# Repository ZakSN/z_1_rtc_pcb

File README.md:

this repo has the kicad board files for the z_1 RTC, a (hopefully very accurate)
real time clock. read more about it here: https://hackaday.io/project/180005-a-digital-real-time-clock

technically this is the 3rd version of the PCBs for this project, howerver the
first 2 versions didn't work well enough to bother publishing.

there are also 3 minor versions of the version 3 PCB:
- 3.1 LCMXO2-1200HC-4SG32C on the board (didn't work for mysterious reasons, see link above)
- 3.2 tinyFPGA-Ax2 module on the board (the tinyFPGA is just a carrier for the LCMX02-1200HC-4SG32C)
- 3.3 LCMXO2-2000HC-5TG100I on the board (same as 3.1, except with parts that are actually in stock right now)

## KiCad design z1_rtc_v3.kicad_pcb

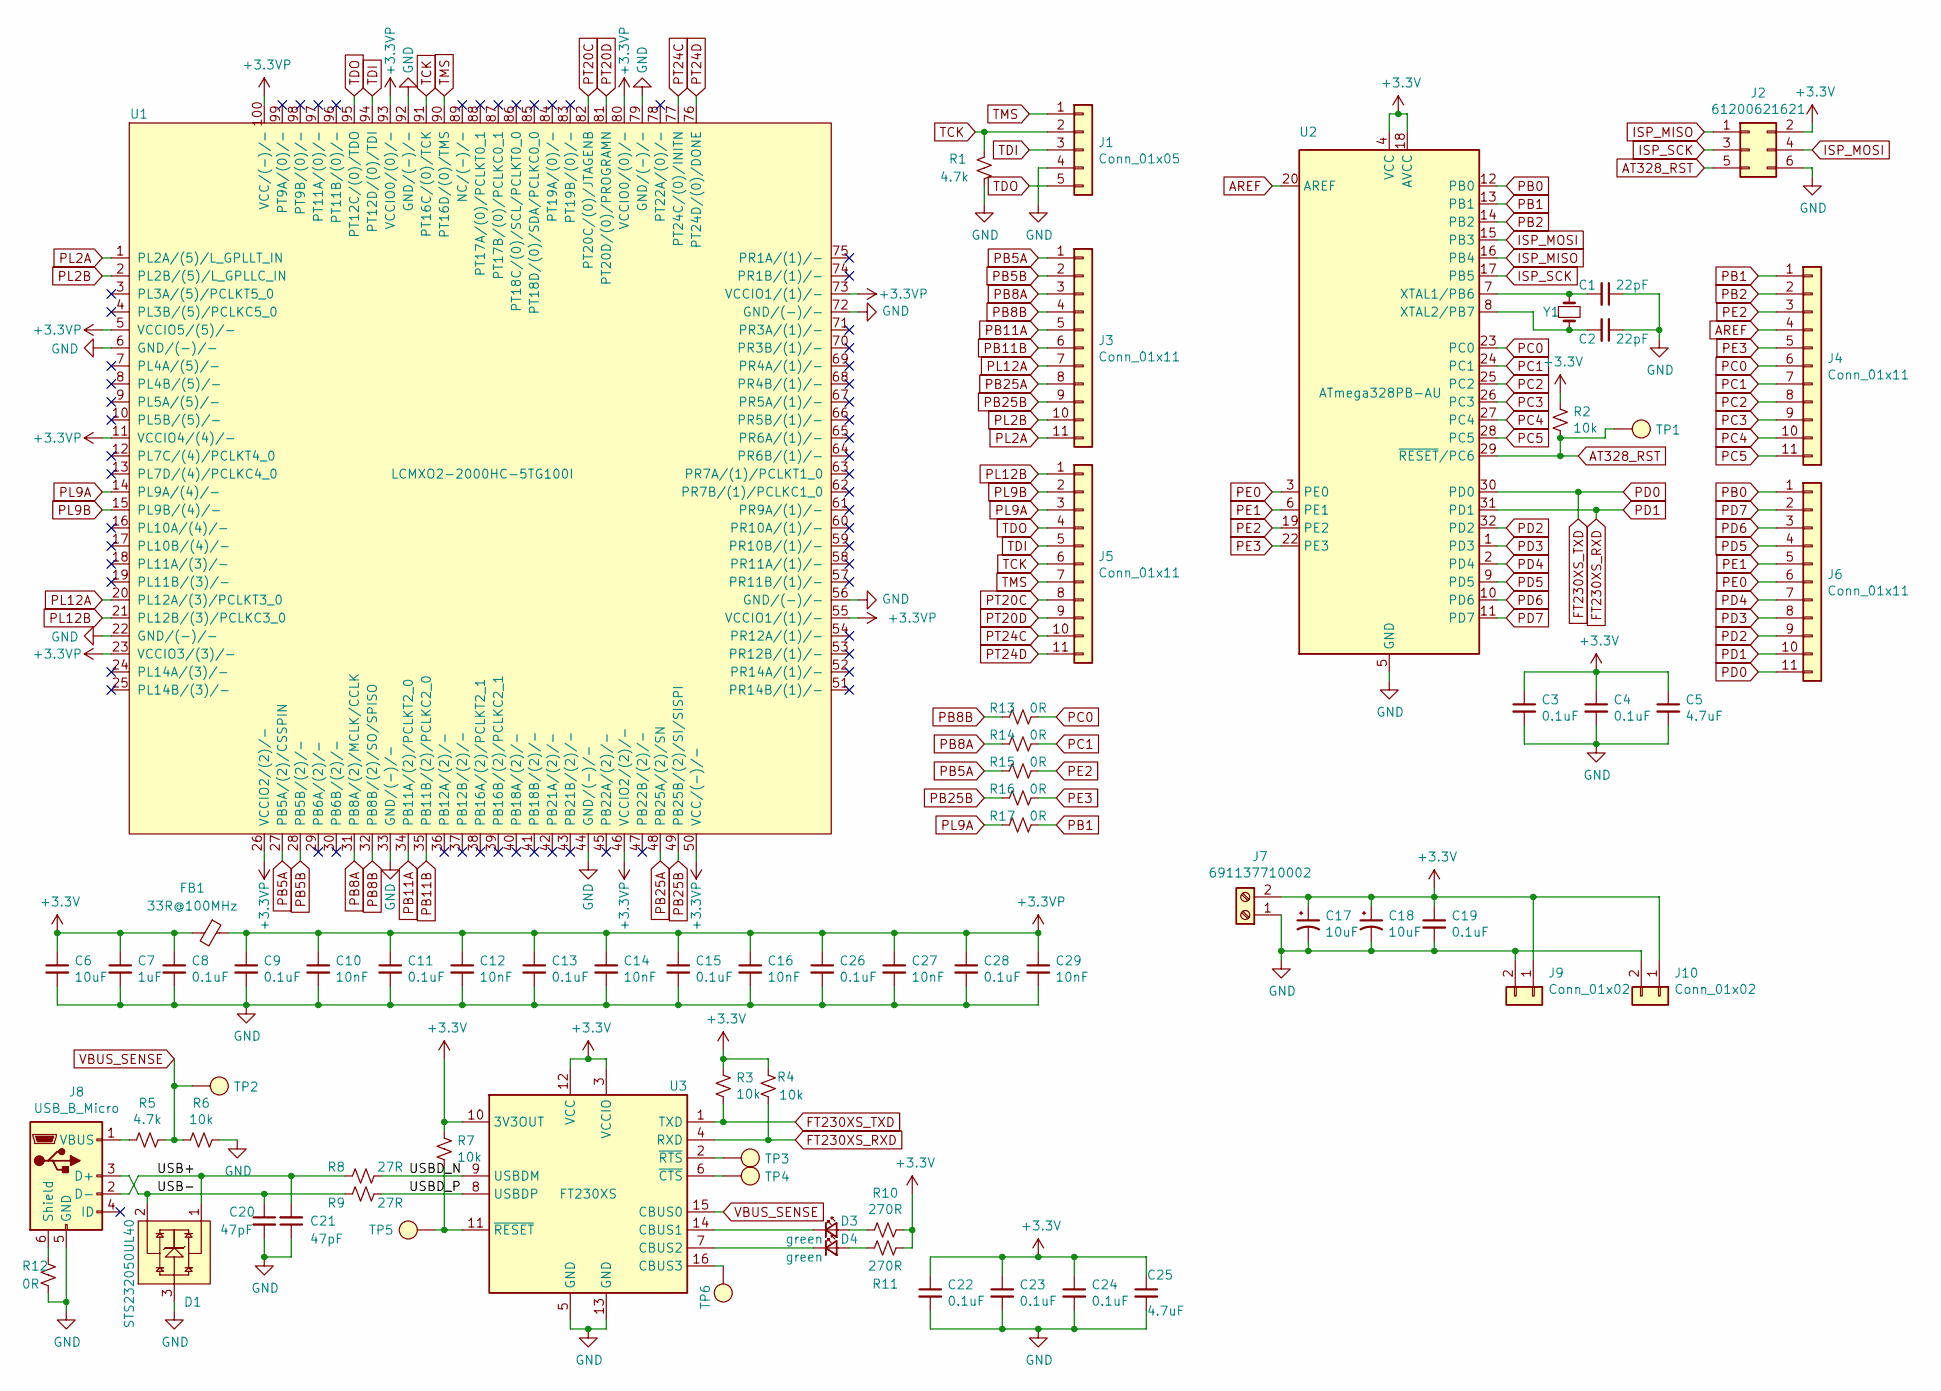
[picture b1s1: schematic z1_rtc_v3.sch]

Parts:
C1, C2: 22pF; C_0603_1608Metric
C3, C4, C8, C9, C11, C13, C15, C19, C22, C23, C24, C26, C28: 0.1uF; C_0603_1608Metric
C5, C25: 4.7uF; C_0603_1608Metric
C6: 10uF; C_0805_2012Metric
C7: 1uF; C_0603_1608Metric
C10, C12, C14, C16, C27, C29: 10nF; C_0805_2012Metric
C17, C18: 10uF; CP_Radial_D8.0mm_P3.80mm
C20, C21: 47pF; C_0603_1608Metric
D1: STS232050UL40; SOT-23
D3, D4: green; LED_0603_1608Metric
FB1: 33R@100MHz; C_0603_1608Metric
J1: Conn_01x05; PinHeader_1x05_P2.54mm_Vertical
J2: 61200621621; PinHeader_2x03_P2.54mm_Vertical
J3, J4, J5, J6: Conn_01x11; PinHeader_1x11_P2.54mm_Vertical
J7: 691137710002
J8: USB_B_Micro; 10118192-0001LF
J9, J10: Conn_01x02; PinHeader_1x02_P2.54mm_Vertical
R1, R5: 4.7k; R_0603_1608Metric
R2, R3, R4, R6, R7: 10k; R_0603_1608Metric
R8, R9: 27R; R_0603_1608Metric
R10, R11: 270R; R_0603_1608Metric
R12, R13, R14, R15, R16, R17: 0R; R_0603_1608Metric
TP1, TP2, TP3, TP4, TP5, TP6: testpoint_smd_circ; test_point_smd_circ
U1: LCMXO2-2000HC-5TG100I; TQFP-100_14x14mm_P0.5mm
U2: ATmega328PB-AU; TQFP-32_7x7mm_P0.8mm
U3: FT230XS; SSOP-16_3.9x4.9mm_P0.635mm
Y1: Crystal_Small; ABLS-8.000MHZ-20-B-3-H-T

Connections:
+3.3VP: C9.1, C10.1, C11.1, C12.1, C13.1, C14.1, C15.1, C16.1, C26.1, C27.1, C28.1, C29.1, FB1.1, U1.5 (VCCIO5/(5)/-), U1.11 (VCCIO4/(4)/-), U1.23 (VCCIO3/(3)/-), U1.26 (VCCIO2/(2)/-), U1.46 (VCCIO2/(2)/-), U1.50 (VCC/(-)/-), U1.55 (VCCIO1/(1)/-), U1.73 (VCCIO1/(1)/-), U1.80 (VCCIO0/(0)/-), U1.93 (VCCIO0/(0)/-), U1.100 (VCC/(-)/-)
+3V3: C3.1, C4.1, C5.1, C6.1, C7.1, C8.1, C17.1, C18.1, C19.1, C22.1, C23.1, C24.1, C25.1, FB1.2, J2.2, J7.2, J9.1, J10.1, R2.1, R3.1, R4.1, R7.1, R10.1, R11.1, U2.4 (VCC), U2.18 (AVCC), U3.3 (VCCIO), U3.10 (3V3OUT), U3.12 (VCC)
/USB+: C21.2, D1.1, J8.2 (D-), R8.2
/USB-: C20.1, D1.2, J8.3 (D+), R9.2
/USBD_N: R8.1, U3.9 (USBDM)
/USBD_P: R9.1, U3.8 (USBDP)
AREF: J4.4, U2.20 (AREF)
AT328_RST: J2.5, R2.2, TP1.~, U2.29 (~RESET~/PC6)
FT230XS_RXD: J6.10, R4.2, U2.31 (PD1), U3.4 (RXD)
FT230XS_TXD: J6.11, R3.2, U2.30 (PD0), U3.1 (TXD)
GND: C1.1, C2.1, C3.2, C4.2, C5.2, C6.2, C7.2, C8.2, C9.2, C10.2, C11.2, C12.2, C13.2, C14.2, C15.2, C16.2, C17.2, C18.2, C19.2, C20.2, C21.1, C22.2, C23.2, C24.2, C25.2, C26.2, C27.2, C28.2, C29.2, D1.3, J1.4, J2.6, J7.1, J8.5 (GND), J9.2, J10.2, R1.2, R6.2, R12.2, U1.6 (GND/(-)/-), U1.22 (GND/(-)/-), U1.33 (GND/(-)/-), U1.44 (GND/(-)/-), U1.56 (GND/(-)/-), U1.72 (GND/(-)/-), U1.79 (GND/(-)/-), U1.92 (GND/(-)/-), U2.5 (GND), U2.21 (GND), U3.5 (GND), U3.13 (GND)
ISP_MISO: J2.1, U2.16 (PB4)
ISP_MOSI: J2.4, U2.15 (PB3)
ISP_SCK: J2.3, U2.17 (PB5)
unnamed: C1.2, U2.7 (XTAL1/PB6), Y1.1
unnamed: C2.2, U2.8 (XTAL2/PB7), Y1.2
unnamed: D3.1 (K), U3.14 (CBUS1)
unnamed: D3.2 (A), R10.2
unnamed: D4.1 (K), U3.7 (CBUS2)
unnamed: D4.2 (A), R11.2
unnamed: J8.1 (VBUS), R5.2
unnamed: J8.6 (Shield), R12.1
unnamed: R7.2, TP5.~, U3.11 (~RESET)
unnamed: TP3.~, U3.2 (~RTS)
unnamed: TP4.~, U3.6 (~CTS)
unnamed: TP6.~, U3.16 (CBUS3)
PB0: J6.1, U2.12 (PB0)
PB1: J4.1, R17.1, U2.13 (PB1)
PB2: J4.2, U2.14 (PB2)
PB5A: J3.1, R15.2, U1.27 (PB5A/(2)/CSSPIN)
PB5B: J3.2, U1.28 (PB5B/(2)/-)
PB8A: J3.3, R14.2, U1.31 (PB8A/(2)/MCLK/CCLK)
PB8B: J3.4, R13.2, U1.32 (PB8B/(2)/SO/SPISO)
PB11A: J3.5, U1.34 (PB11A/(2)/PCLKT2_0)
PB11B: J3.6, U1.35 (PB11B/(2)/PCLKC2_0)
PB25A: J3.8, U1.48 (PB25A/(2)/SN)
PB25B: J3.9, R16.2, U1.49 (PB25B/(2)/SI/SISPI)
PC0: J4.6, R13.1, U2.23 (PC0)
PC1: J4.7, R14.1, U2.24 (PC1)
PC2: J4.8, U2.25 (PC2)
PC3: J4.9, U2.26 (PC3)
PC4: J4.10, U2.27 (PC4)
PC5: J4.11, U2.28 (PC5)
PD2: J6.9, U2.32 (PD2)
PD3: J6.8, U2.1 (PD3)
PD4: J6.7, U2.2 (PD4)
PD5: J6.4, U2.9 (PD5)
PD6: J6.3, U2.10 (PD6)
PD7: J6.2, U2.11 (PD7)
PE0: J6.6, U2.3 (PE0)
PE1: J6.5, U2.6 (PE1)
PE2: J4.3, R15.1, U2.19 (PE2)
PE3: J4.5, R16.1, U2.22 (PE3)
PL2A: J3.11, U1.1 (PL2A/(5)/L_GPLLT_IN)
PL2B: J3.10, U1.2 (PL2B/(5)/L_GPLLC_IN)
PL9A: J5.3, R17.2, U1.14 (PL9A/(4)/-)
PL9B: J5.2, U1.15 (PL9B/(4)/-)
PL12A: J3.7, U1.20 (PL12A/(3)/PCLKT3_0)
PL12B: J5.1, U1.21 (PL12B/(3)/PCLKC3_0)
PT20C: J5.8, U1.82 (PT20C/(0)/JTAGENB)
PT20D: J5.9, U1.81 (PT20D/(0)/PROGRAMN)
PT24C: J5.10, U1.77 (PT24C/(0)/INITN)
PT24D: J5.11, U1.76 (PT24D/(0)/DONE)
TCK: J1.2, J5.6, R1.1, U1.91 (PT16C/(0)/TCK)
TDI: J1.3, J5.5, U1.94 (PT12D/(0)/TDI)
TDO: J1.5, J5.4, U1.95 (PT12C/(0)/TDO)
TMS: J1.1, J5.7, U1.90 (PT16D/(0)/TMS)
VBUS_SENSE: R5.1, R6.1, TP2.~, U3.15 (CBUS0)

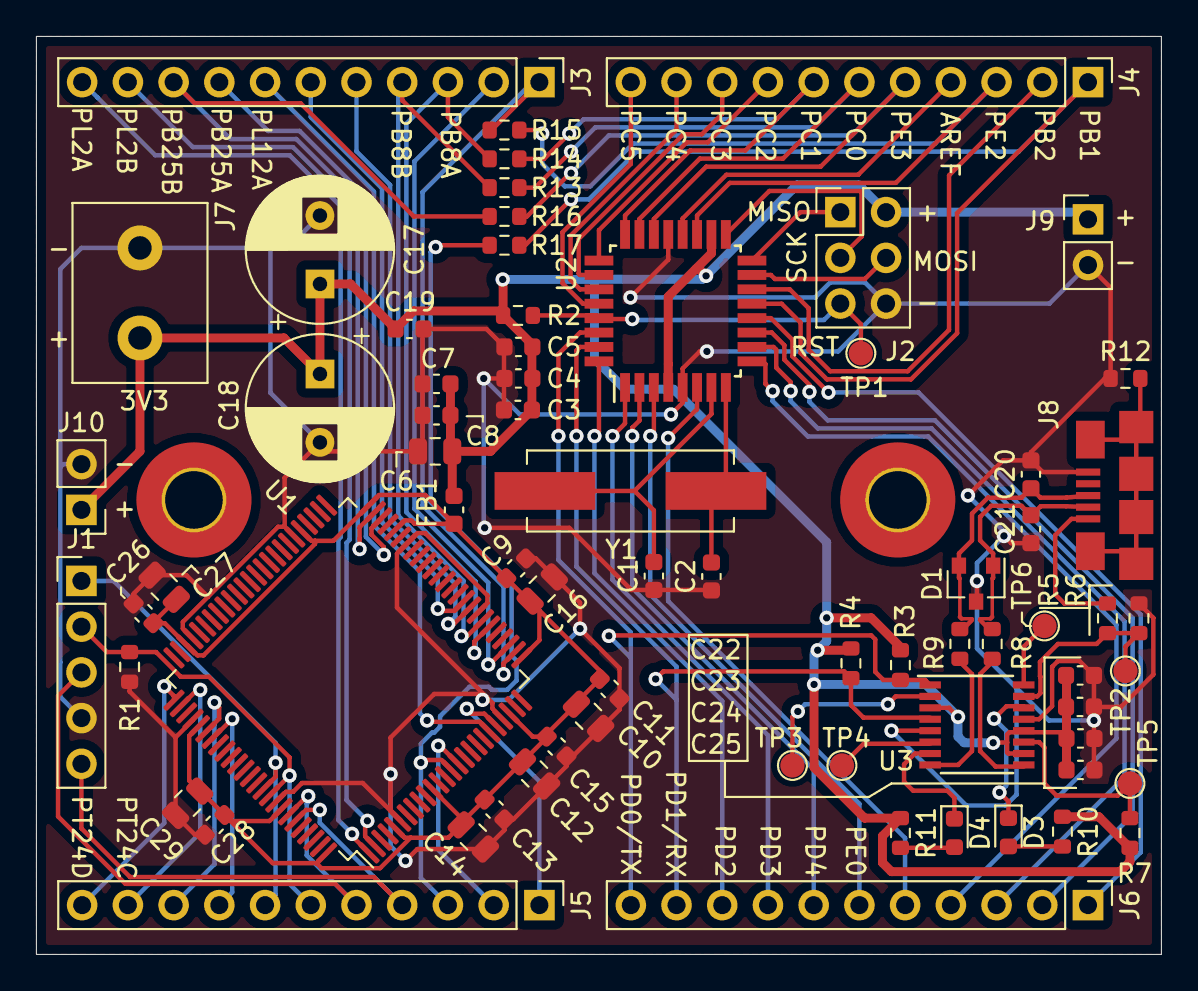
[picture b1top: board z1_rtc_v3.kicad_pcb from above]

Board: 2 copper layers, 62.5 x 51.0 mm, 70 parts (0 on the bottom side), 68 nets.

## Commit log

2021-06-14 initial commit -- v3.1 board
2021-06-17 board files for v3.2, with the tinyFPGA module
2021-06-17 fix library links in main kicad project, and add readme
2021-06-19 finished routing v3.3
2021-06-20 finish silks
